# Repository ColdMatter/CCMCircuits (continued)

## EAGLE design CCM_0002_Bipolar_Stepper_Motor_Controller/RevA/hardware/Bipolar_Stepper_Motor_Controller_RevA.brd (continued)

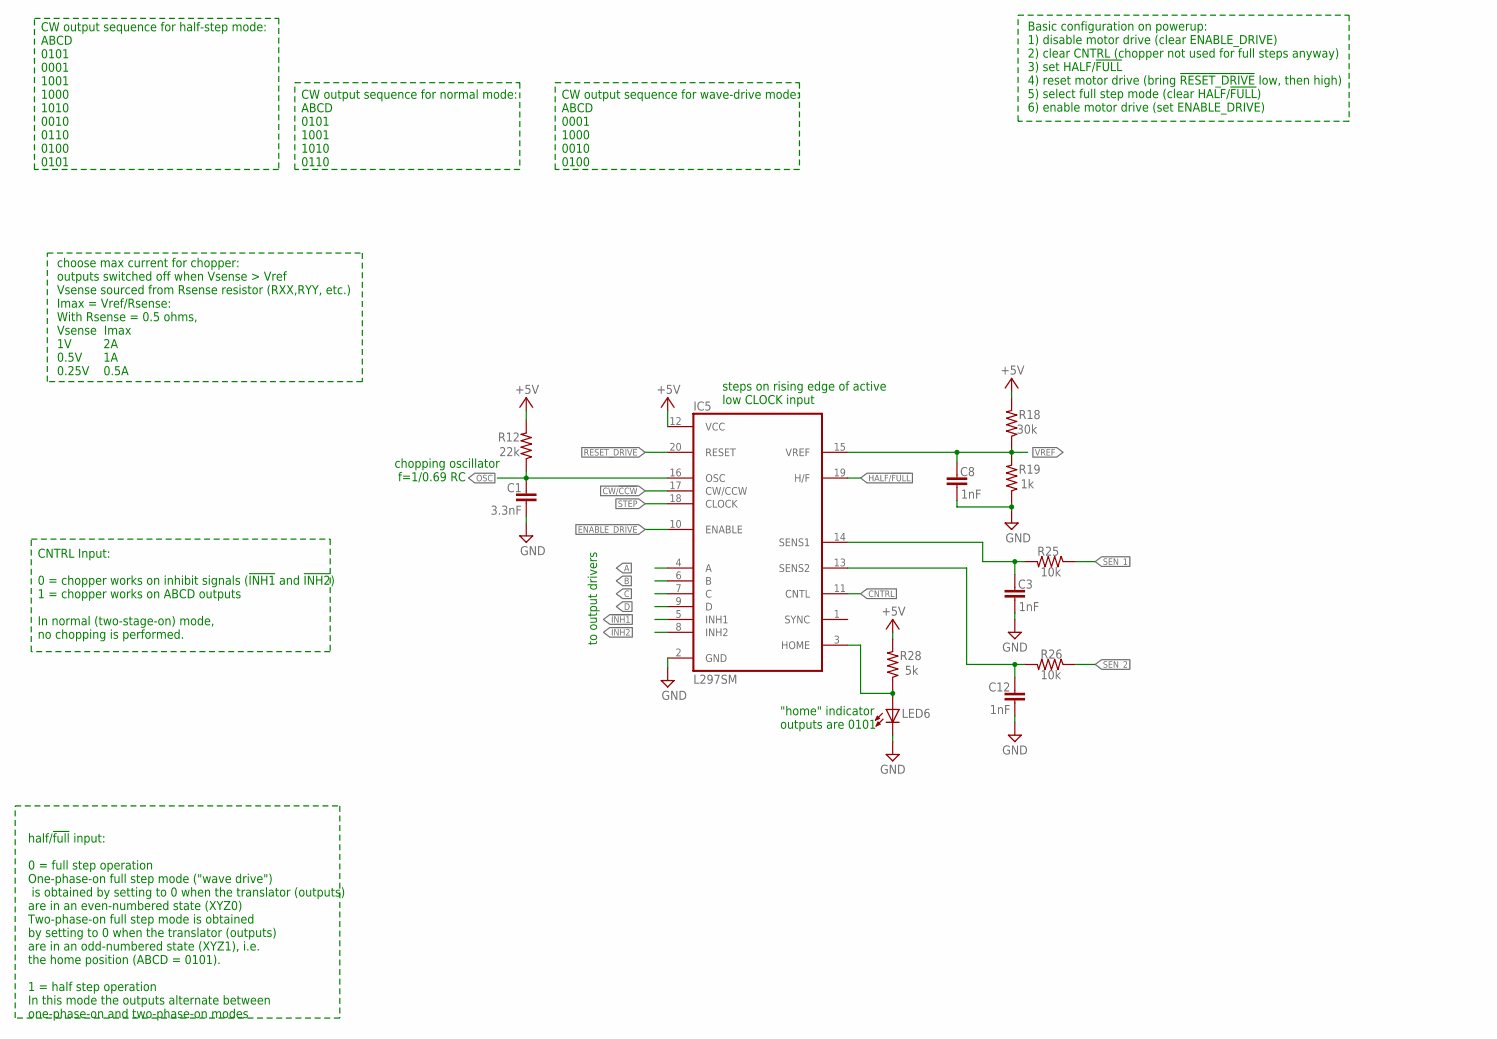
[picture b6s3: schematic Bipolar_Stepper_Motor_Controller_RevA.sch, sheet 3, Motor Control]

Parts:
C1: 3.3nF; 0603-CAP
C3, C8, C12: 1nF; 0603-CAP
IC5: L297SM; SO20
LED6: red; CHIPLED_0603
R12: 22k; 0603-RES
R18: 30k; 0603-RES
R19: 1k; 0603-RES
R25, R26: 10k; 0603-RES
R28: 5k; 0603-RES

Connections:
!INH1: IC5.5 (INH1); also elsewhere on the board
!INH2: IC5.8 (INH2); also elsewhere on the board
!RESET_DRIVE: IC5.20 (RESET); also elsewhere on the board
+5V: IC5.12 (VCC), R12.2, R18.2, R28.2; also elsewhere on the board
A: IC5.4 (A); also elsewhere on the board
B: IC5.6 (B); also elsewhere on the board
C: IC5.7 (C); also elsewhere on the board
CNTRL: IC5.11 (CNTL); also elsewhere on the board
CW/!CCW: IC5.17 (CW/CCW); also elsewhere on the board
D: IC5.9 (D); also elsewhere on the board
ENABLE_DRIVE: IC5.10 (ENABLE); also elsewhere on the board
GND: C1.2, C3.2, C8.2, C12.2, IC5.2 (GND), LED6.C, R19.1; also elsewhere on the board
HALF/!FULL: IC5.19 (H/F); also elsewhere on the board
unnamed: IC5.3 (HOME), LED6.A, R28.1
OSC: C1.1, IC5.16 (OSC), R12.1
SENSE1: C3.1, IC5.14 (SENS1), R25.2
SENSE2: C12.1, IC5.13 (SENS2), R26.2
SEN_1: R25.1; also elsewhere on the board
SEN_2: R26.1; also elsewhere on the board
STEP: IC5.18 (CLOCK); also elsewhere on the board
VREF: C8.1, IC5.15 (VREF), R18.1, R19.2

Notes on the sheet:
chopping oscillator f=1/0.69 RC
steps on rising edge of active low CLOCK input
choose max current for chopper: outputs switched off when Vsense > Vref Vsense sourced from Rsense resistor (RXX,RYY, etc.) Imax = Vref/Rsense: With Rsense = 0.5 ohms, Vsense Imax 1V 2A 0.5V 1A 0.25V 0.5A
"home" indicator outputs are 0101
to output drivers
CNTRL Input: 0 = chopper works on inhibit signals (!INH1! and !INH2!) 1 = chopper works on ABCD outputs In normal (two-stage-on) mode, no chopping is performed.
half/!full! input: 0 = full step operation One-phase-on full step mode ("wave drive") is obtained by setting to 0 when the translator (outputs) are in an even-numbered state (XYZ0) Two-phase-on full step mode is obtained by setting to 0 when the translator (outputs) are in an odd-numbered state (XY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
CW output sequence for half-step mode: ABCD 0101 0001 1001 1000 1010 0010 0110 0100 0101
Basic configuration on powerup: 1) disable motor drive (clear ENABLE_DRIVE) 2) clear CNTRL (chopper not used for full steps anyway) 3) set HALF/!FULL! 4) reset motor drive (bring !RESET_DRIVE! low, then high) 5) select full step mode (clear HALF/!FULL!) 6) enable motor drive (set ENABLE_DRIVE)
CW output sequence for normal mode: ABCD 0101 1001 1010 0110
CW output sequence for wave-drive mode: ABCD 0001 1000 0010 0100

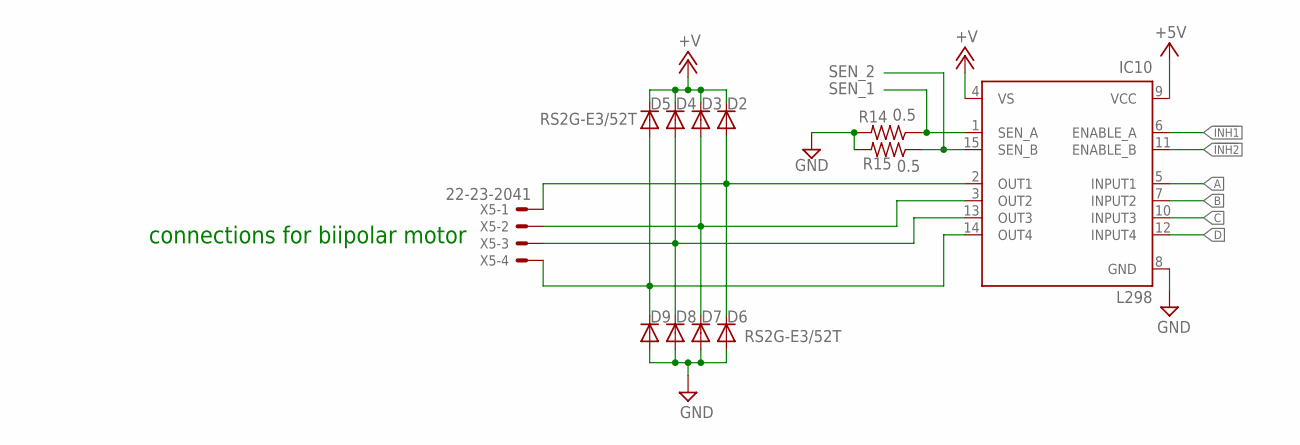
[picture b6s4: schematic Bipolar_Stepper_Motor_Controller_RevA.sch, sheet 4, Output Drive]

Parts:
D2, D3, D4, D5, D6, D7, D8, D9: RS2G-E3/52T; DO214AA
IC10: L298; MULTIWATT-15
R14, R15: 0.5; R2512
X5: 22-23-2041

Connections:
!INH1: IC10.6 (ENABLE_A); also elsewhere on the board
!INH2: IC10.11 (ENABLE_B); also elsewhere on the board
+5V: IC10.9 (VCC); also elsewhere on the board
+V: D2.C, D3.C, D4.C, D5.C, IC10.4 (VS); also elsewhere on the board
A: IC10.5 (INPUT1); also elsewhere on the board
B: IC10.7 (INPUT2); also elsewhere on the board
BI_A: D2.A, D6.C, IC10.2 (OUT1), X5.1
BI_B: D3.A, D7.C, IC10.3 (OUT2), X5.2
BI_C: D4.A, D8.C, IC10.13 (OUT3), X5.3
BI_D: D5.A, D9.C, IC10.14 (OUT4), X5.4
C: IC10.10 (INPUT3); also elsewhere on the board
D: IC10.12 (INPUT4); also elsewhere on the board
GND: D6.A, D7.A, D8.A, D9.A, IC10.8 (GND), R14.2, R15.2; also elsewhere on the board
SEN_1: IC10.1 (SEN_A), R14.1; also elsewhere on the board
SEN_2: IC10.15 (SEN_B), R15.1; also elsewhere on the board

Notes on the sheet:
connections for biipolar motor

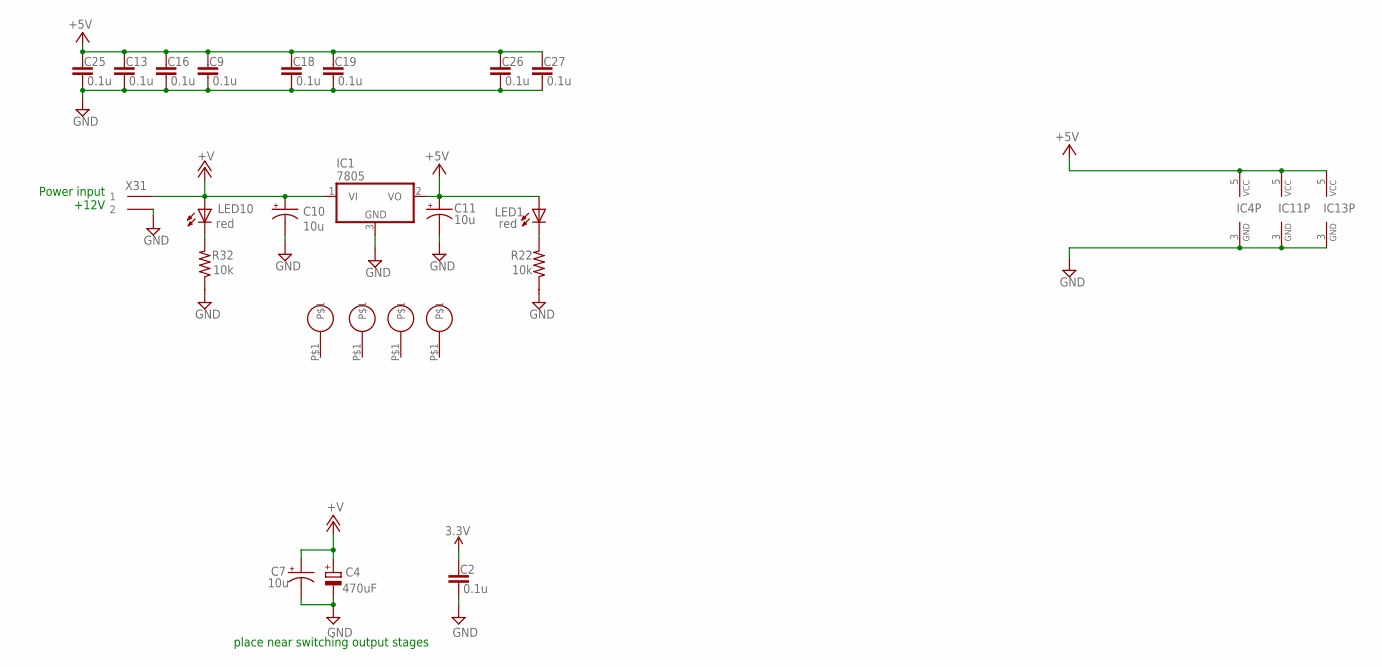
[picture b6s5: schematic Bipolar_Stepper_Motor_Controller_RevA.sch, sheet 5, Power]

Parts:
C2, C9, C13, C16, C18, C19, C25, C26, C27: 0.1u; 0603-CAP
C4: 470uF; SANYO-OSCON_SMD_F8
C7, C10, C11: 10u; EIA3216
IC1: 7805; TO252
IC4, IC11, IC13: 74AHC1G08DBV; SOT23-5
LED1, LED10: red; CHIPLED_0805
R22, R32: 10k; 0805
U$1, U$2, U$3, U$4: 2-56
X31: SL_70543_2

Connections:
3.3V: C2.1; also elsewhere on the board
+5V: C9.1, C11.A (+), C13.1, C16.1, C18.1, C19.1, C25.1, C26.1, C27.1, IC1.2 (VO), IC4.5 (VCC), IC11.5 (VCC), IC13.5 (VCC), LED1.A; also elsewhere on the board
+V: C4.+, C7.A (+), C10.A (+), IC1.1 (VI), LED10.A, X31.P$1 (1); also elsewhere on the board
GND: C2.2, C4.-, C7.C (-), C9.2, C10.C (-), C11.C (-), C13.2, C16.2, C18.2, C19.2, C25.2, C26.2, C27.2, IC1.3 (GND), IC4.3 (GND), IC11.3 (GND), IC13.3 (GND), R22.1, R32.1, X31.P$2 (2); also elsewhere on the board
LED1: LED1.C, R22.2
LED5: LED10.C, R32.2

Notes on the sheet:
Power input +12V
place near switching output stages

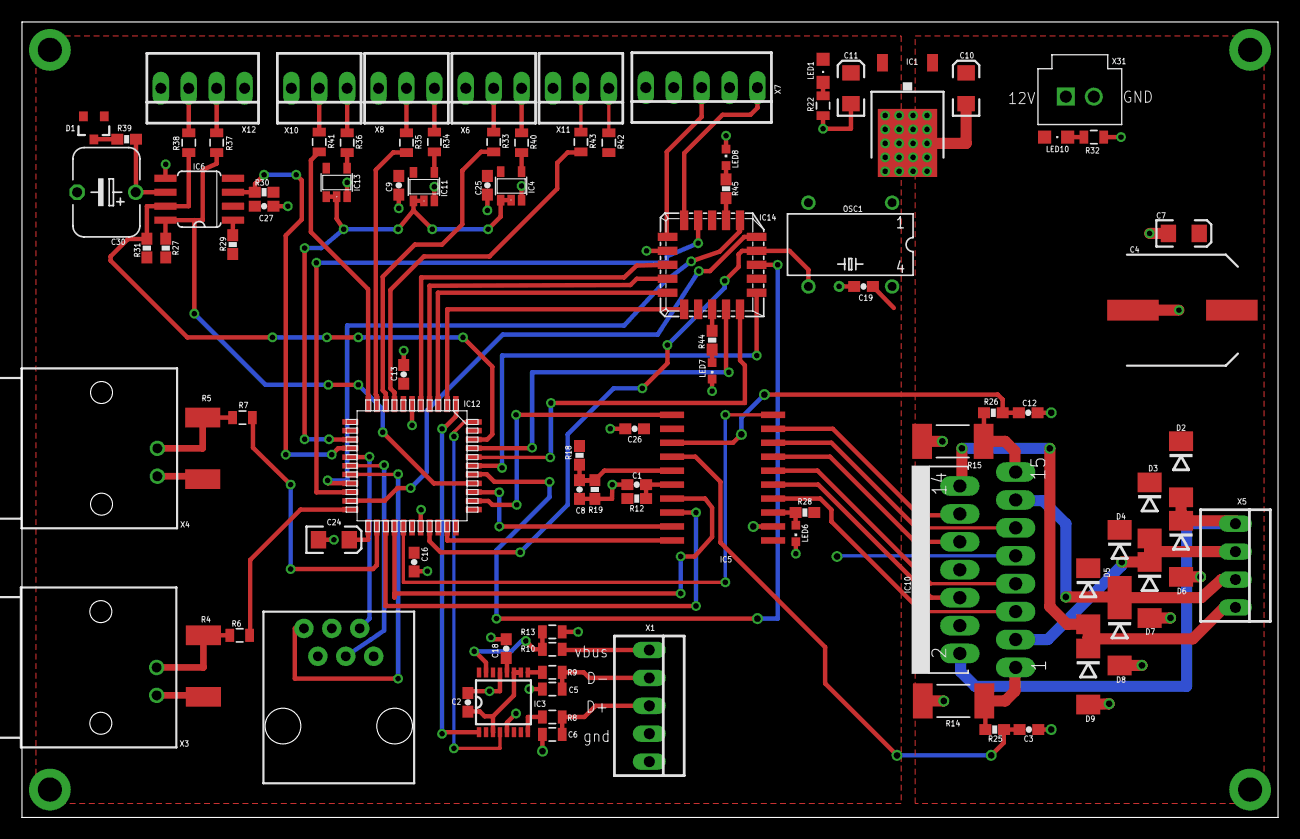
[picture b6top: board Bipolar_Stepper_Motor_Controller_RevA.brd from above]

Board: 2 copper layers, 114.3 x 72.4 mm, 97 parts (0 on the bottom side), 87 nets.

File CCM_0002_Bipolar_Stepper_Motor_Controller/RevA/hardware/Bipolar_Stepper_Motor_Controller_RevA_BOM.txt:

Partlist exported from C:/Users/nfitch/Google Drive/Electronics/Projects/CCM_0002_Bipolar_Stepper_Motor_Controller/RevA/Circuit/Bipolar_Stepper_Motor_Controller_RevA.sch at 10/11/2014 11:08:58

Qty Value        Device              Package            Parts                                     Description                                           
1   0.1F         CPOL-USP128-60      P128-60            C30                                       POLARIZED CAPACITOR, American symbol                  
9   0.1u         CAP0603-CAP         0603-CAP           C2, C9, C13, C16, C18, C19, C25, C26, C27 Capacitor                                             
2   0.5          R-US_R2512          R2512              R14, R15                                  RESISTOR, American symbol                             
2   1-227161-0   1-227161-0          AMP_227161         X3, X4                                    JACK,  RIGHT ANGLE, 50 OHM, PCB, BNC                  
3   10k          RESISTOR            0805               R13, R22, R32                             Resistor                                              
5   10k          RESISTOR0603-RES    0603-RES           R25, R26, R29, R30, R39                   Resistor                                              
4   10u          CAP_POL1206         EIA3216            C7, C10, C11, C24                         Capacitor Polarized                                   
8   1k           RESISTOR            0805               R6, R7, R33, R35, R37, R38, R41, R43      Resistor                                              
1   1k           RESISTOR0603-RES    0603-RES           R19                                       Resistor                                              
3   1nF          CAP0603-CAP         0603-CAP           C3, C8, C12                               Capacitor                                             
4   2-56         2-56                2-56               U$1, U$2, U$3, U$4                                                                              
4   22-23-2031   22-23-2031          22-23-2031         X6, X8, X10, X11                          .100" (2.54mm) Center Header - 3 Pin                  
2   22-23-2041   22-23-2041          22-23-2041         X5, X12                                   .100" (2.54mm) Center Header - 4 Pin                  
2   22-23-2051   22-23-2051          22-23-2051         X1, X7                                    .100" (2.54mm) Center Header - 5 Pin                  
1   22k          RESISTOR0603-RES    0603-RES           R12                                       Resistor                                              
2   27           RESISTOR            0805               R8, R9                                    Resistor                                              
1   3.3nF        CAP0603-CAP         0603-CAP           C1                                        Capacitor                                             
4   300          RESISTOR            0805               R34, R36, R40, R42                        Resistor                                              
1   30k          RESISTOR0603-RES    0603-RES           R18                                       Resistor                                              
1   4.7k         RESISTOR            0805               R10                                       Resistor                                              
2   4.7k         RESISTOR0603-RES    0603-RES           R27, R31                                  Resistor                                              
1   4148         DIODESOT23          SOT23-3            D1                                        Diode                                                 
1   470uF        CPOL-EUSANYO_SMD_F8 SANYO-OSCON_SMD_F8 C4                                        POLARIZED CAPACITOR, European symbol                  
2   47p          CAP0805             0805               C5, C6                                    Capacitor                                             
2   50           R-US_R2512          R2512              R4, R5                                    RESISTOR, American symbol                             
3   5k           RESISTOR0603-RES    0603-RES           R28, R44, R45                             Resistor                                              
3   74AHC1G08DBV 74AHC1G08DBV        SOT23-5            IC4, IC11, IC13                           2-input AND gate                                      
1   7805         7824DT              TO252              IC1                                       Positive VOLTAGE REGULATOR                            
1   DS3231M      DS3231M             8-SOIC             IC6                                       RTC (real time clock), I2C communication              
1   FT230XS      FT230XS             SSOP16             IC3                                       USB to BASIC UART IC                                  
1   HCTL-2021    HCTL-2021           PLCC20             IC14                                      HCTL-2021 Quadrature decoder from Avago Technologies. 
1   L297SM       L297SM              SO20               IC5                                       STEPPER MOTOR CONTROLLER                              
1   L298         L298                MULTIWATT-15       IC10                                      DUAL FULL-BRIDGE DRIVER                               
1   MX045-4MHz   SG531               DIL08-4            OSC1                                      CRYSTAL RESONATOR                                     
1   PIC18F46K80  PIC18F46K80         TQFP44_MC          IC12                                                                                            
1   RJ11-6PTH    RJ11-6PTH           RJ11-6             J1                                        RJ11 Jack                                             
8   RS2G-E3/52T  DIODE-DO214AA       DO214AA            D2, D3, D4, D5, D6, D7, D8, D9            DIODE                                                 
1   SL_70543_2   SL_70543_2          SL_70543_2         X31                                                                                             
3   red          LEDCHIPLED_0603     CHIPLED_0603       LED6, LED7, LED8                          LED                                                   
2   red          LEDCHIPLED_0805     CHIPLED_0805       LED1, LED10                               LED

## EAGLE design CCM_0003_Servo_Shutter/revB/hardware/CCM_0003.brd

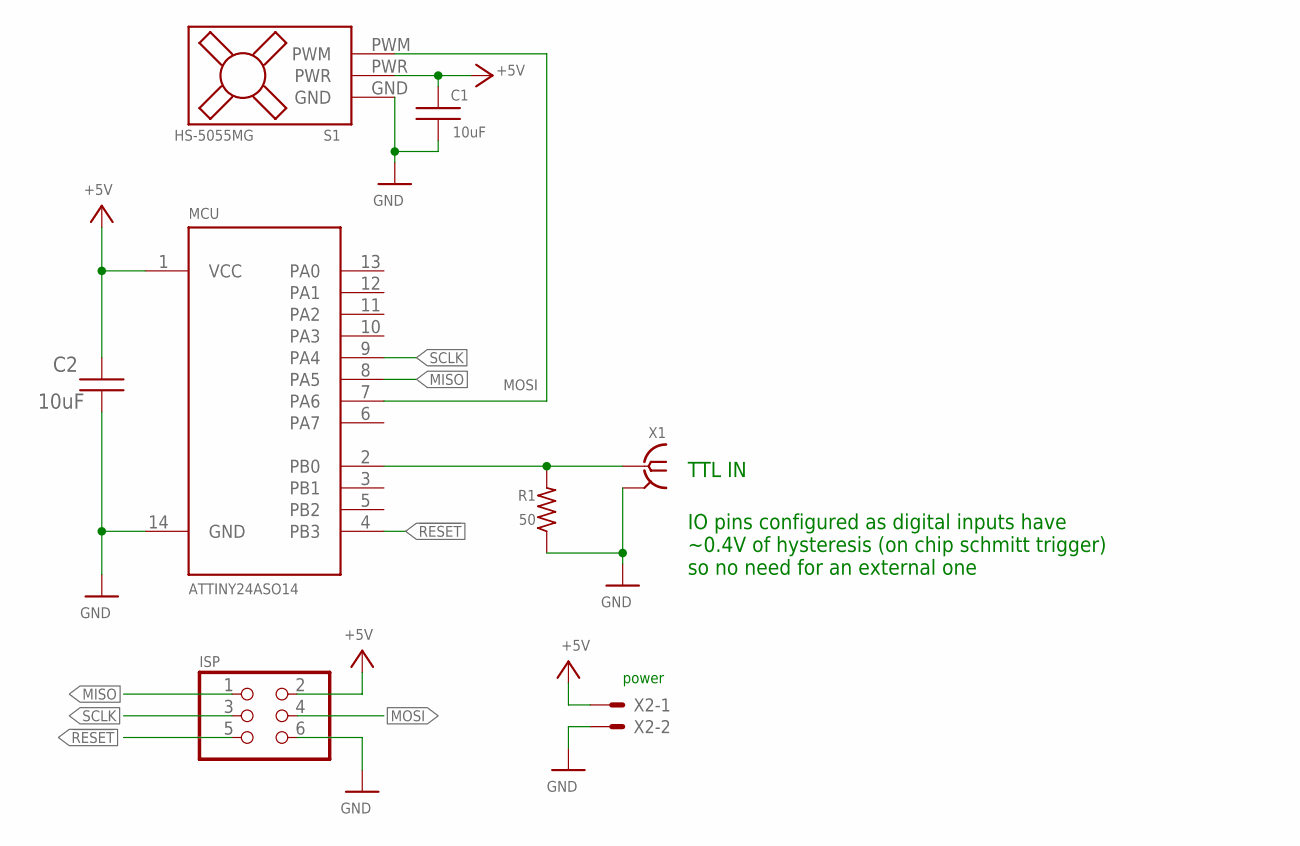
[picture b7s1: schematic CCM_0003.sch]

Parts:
C1, C2: 10uF; 0603
ISP: ISP; 2X03
MCU: ATTINY24ASO14; SO14
R1: 50; R2010
S1: HS-5055MG
X1: BU-SMA-H
X2: 22-23-2021

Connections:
!RESET: ISP.5, MCU.4 (PB3)
+5V: C1.1, C2.1, ISP.2, MCU.1 (VCC), S1.PWR, X2.1
GND: C1.2, C2.2, ISP.6, MCU.14 (GND), R1.1, S1.GND, X1.2, X1.3 (2), X1.4 (2), X1.5 (2), X2.2
MISO: ISP.1, MCU.8 (PA5)
MOSI: ISP.4, MCU.7 (PA6), S1.PWM
SCLK: ISP.3, MCU.9 (PA4)
TTL: MCU.2 (PB0), R1.2, X1.1

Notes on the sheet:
TTL IN
power
IO pins configured as digital inputs have ~0.4V of hysteresis (on chip schmitt trigger) so no need for an external one

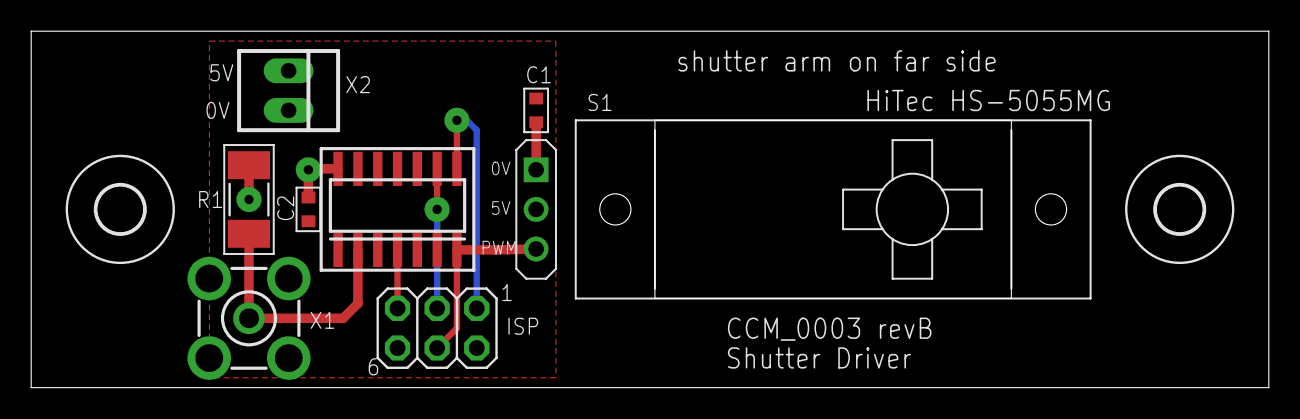
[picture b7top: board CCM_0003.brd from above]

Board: 2 copper layers, 79.4 x 22.9 mm, 10 parts (0 on the bottom side), 7 nets.

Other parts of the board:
U$1, U$3: 3,0
